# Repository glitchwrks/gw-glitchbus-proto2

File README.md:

Glitchbus Prototyping Board
===========================

This project is a prototyping board for Glitchbus, which is used on several of our SBC projects. It provides a pad-per-hole board with dedicated areas for the Glitchbus. All signal pins are labeled on front and back. It is compatible with both stacking and backplane configurations, and will accomodate wire wrapping.

Aside from being a useful prototyping board, this project can be used as the starting point for a custom Glitchbus PCBs.

License
-------

This project is released under the GNU GPLv3, a copy of which should be included with the project files.

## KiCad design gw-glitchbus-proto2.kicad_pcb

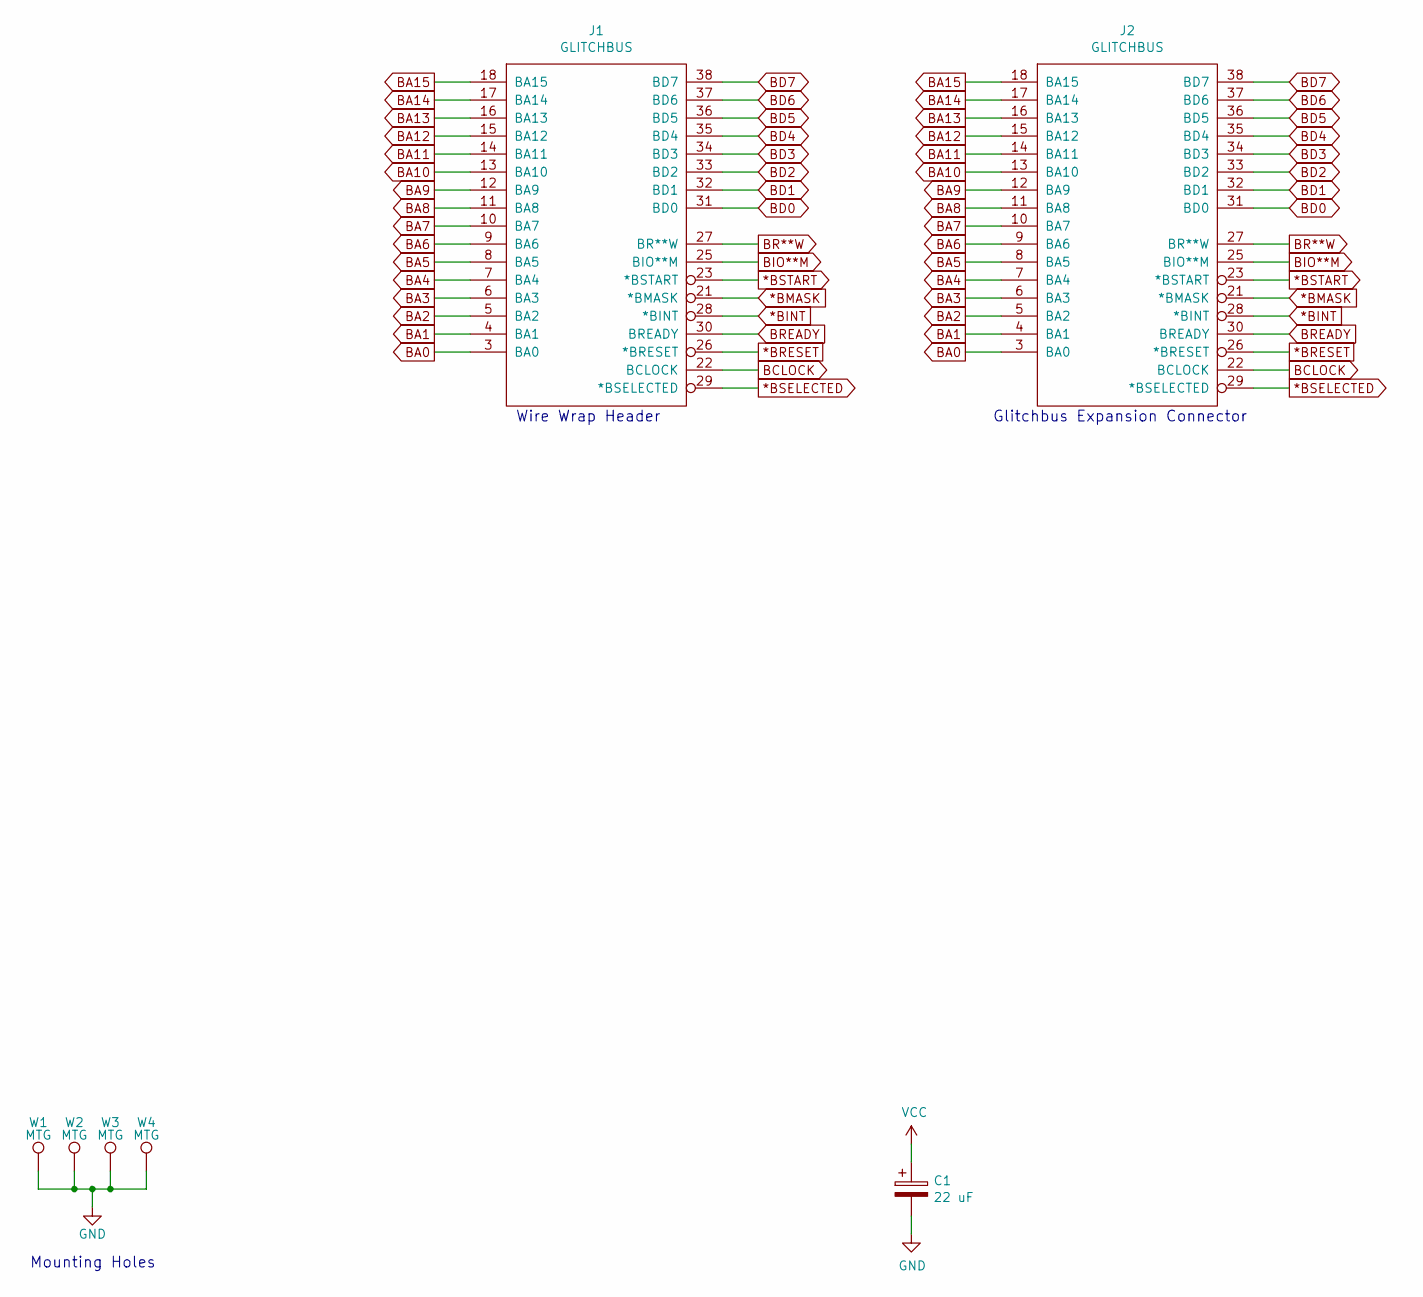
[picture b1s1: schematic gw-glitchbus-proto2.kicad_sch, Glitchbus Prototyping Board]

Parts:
C1: 22 uF; CP_AX_700_200
J1, J2: GLITCHBUS; STRAIGHT_2x20
W1, W2, W3, W4: MTG; 120mil_no_silkscreen

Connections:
*BINT: J1.28 (*BINT), J2.28 (*BINT)
*BMASK: J1.21 (*BMASK), J2.21 (*BMASK)
*BRESET: J1.26 (*BRESET), J2.26 (*BRESET)
*BSELECTED: J1.29 (*BSELECTED), J2.29 (*BSELECTED)
*BSTART: J1.23 (*BSTART), J2.23 (*BSTART)
BA0: J1.3 (BA0), J2.3 (BA0)
BA1: J1.4 (BA1), J2.4 (BA1)
BA2: J1.5 (BA2), J2.5 (BA2)
BA3: J1.6 (BA3), J2.6 (BA3)
BA4: J1.7 (BA4), J2.7 (BA4)
BA5: J1.8 (BA5), J2.8 (BA5)
BA6: J1.9 (BA6), J2.9 (BA6)
BA7: J1.10 (BA7), J2.10 (BA7)
BA8: J1.11 (BA8), J2.11 (BA8)
BA9: J1.12 (BA9), J2.12 (BA9)
BA10: J1.13 (BA10), J2.13 (BA10)
BA11: J1.14 (BA11), J2.14 (BA11)
BA12: J1.15 (BA12), J2.15 (BA12)
BA13: J1.16 (BA13), J2.16 (BA13)
BA14: J1.17 (BA14), J2.17 (BA14)
BA15: J1.18 (BA15), J2.18 (BA15)
BCLOCK: J1.22 (BCLOCK), J2.22 (BCLOCK)
BD0: J1.31 (BD0), J2.31 (BD0)
BD1: J1.32 (BD1), J2.32 (BD1)
BD2: J1.33 (BD2), J2.33 (BD2)
BD3: J1.34 (BD3), J2.34 (BD3)
BD4: J1.35 (BD4), J2.35 (BD4)
BD5: J1.36 (BD5), J2.36 (BD5)
BD6: J1.37 (BD6), J2.37 (BD6)
BD7: J1.38 (BD7), J2.38 (BD7)
BIO**M: J1.25 (BIO**M), J2.25 (BIO**M)
BR**W: J1.27 (BR**W), J2.27 (BR**W)
BREADY: J1.30 (BREADY), J2.30 (BREADY)
GND: C1.2, J1.19 (GND), J1.20 (GND), J1.24 (GND), J1.39 (GND), J1.40 (GND), J2.19 (GND), J2.20 (GND), J2.24 (GND), J2.39 (GND), J2.40 (GND), W1.1, W2.1, W3.1, W4.1
VCC: C1.1, J1.1 (VCC), J1.2 (VCC), J2.1 (VCC), J2.2 (VCC)

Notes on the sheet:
Mounting Holes
Glitchbus Expansion Connector
Wire Wrap Header

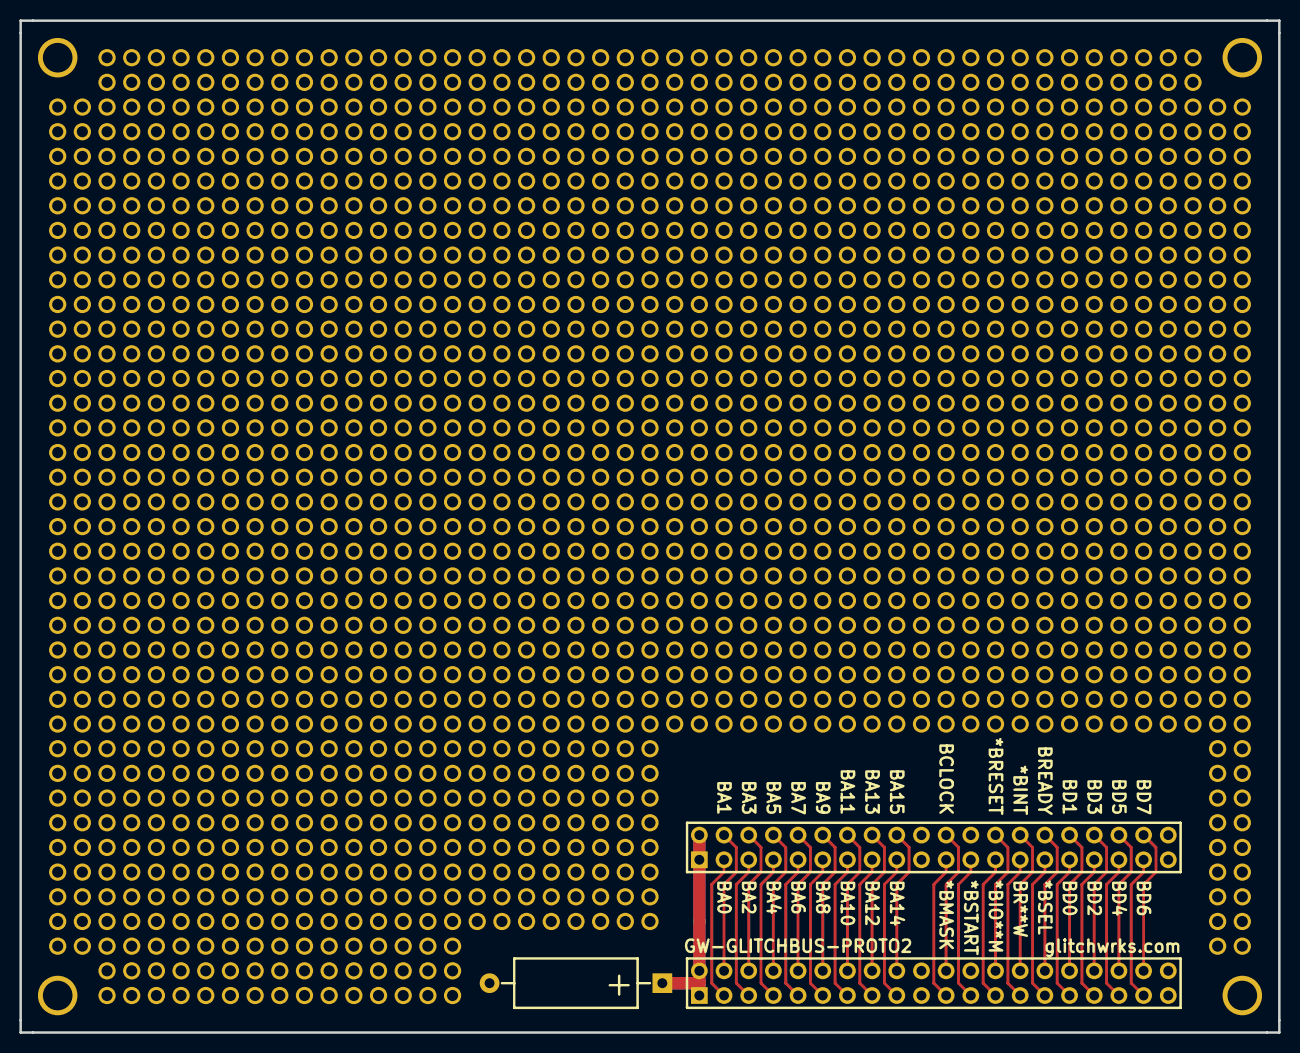
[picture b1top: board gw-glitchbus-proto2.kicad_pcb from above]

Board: 2 copper layers, 129.5 x 104.1 mm, 7 parts (0 on the bottom side), 35 nets.

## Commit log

2024-01-24 Updating schematic for *BSELECTED, new library paths
2024-01-24 Adding license, README
2024-11-12 Updating to KiCAD 8
2024-11-12 Removing extraneous files
